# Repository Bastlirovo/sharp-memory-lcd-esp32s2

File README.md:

# sharp-memory-lcd-esp32s2
Project for ESP32-S2 devboard with connector for Sharp Memory LCD

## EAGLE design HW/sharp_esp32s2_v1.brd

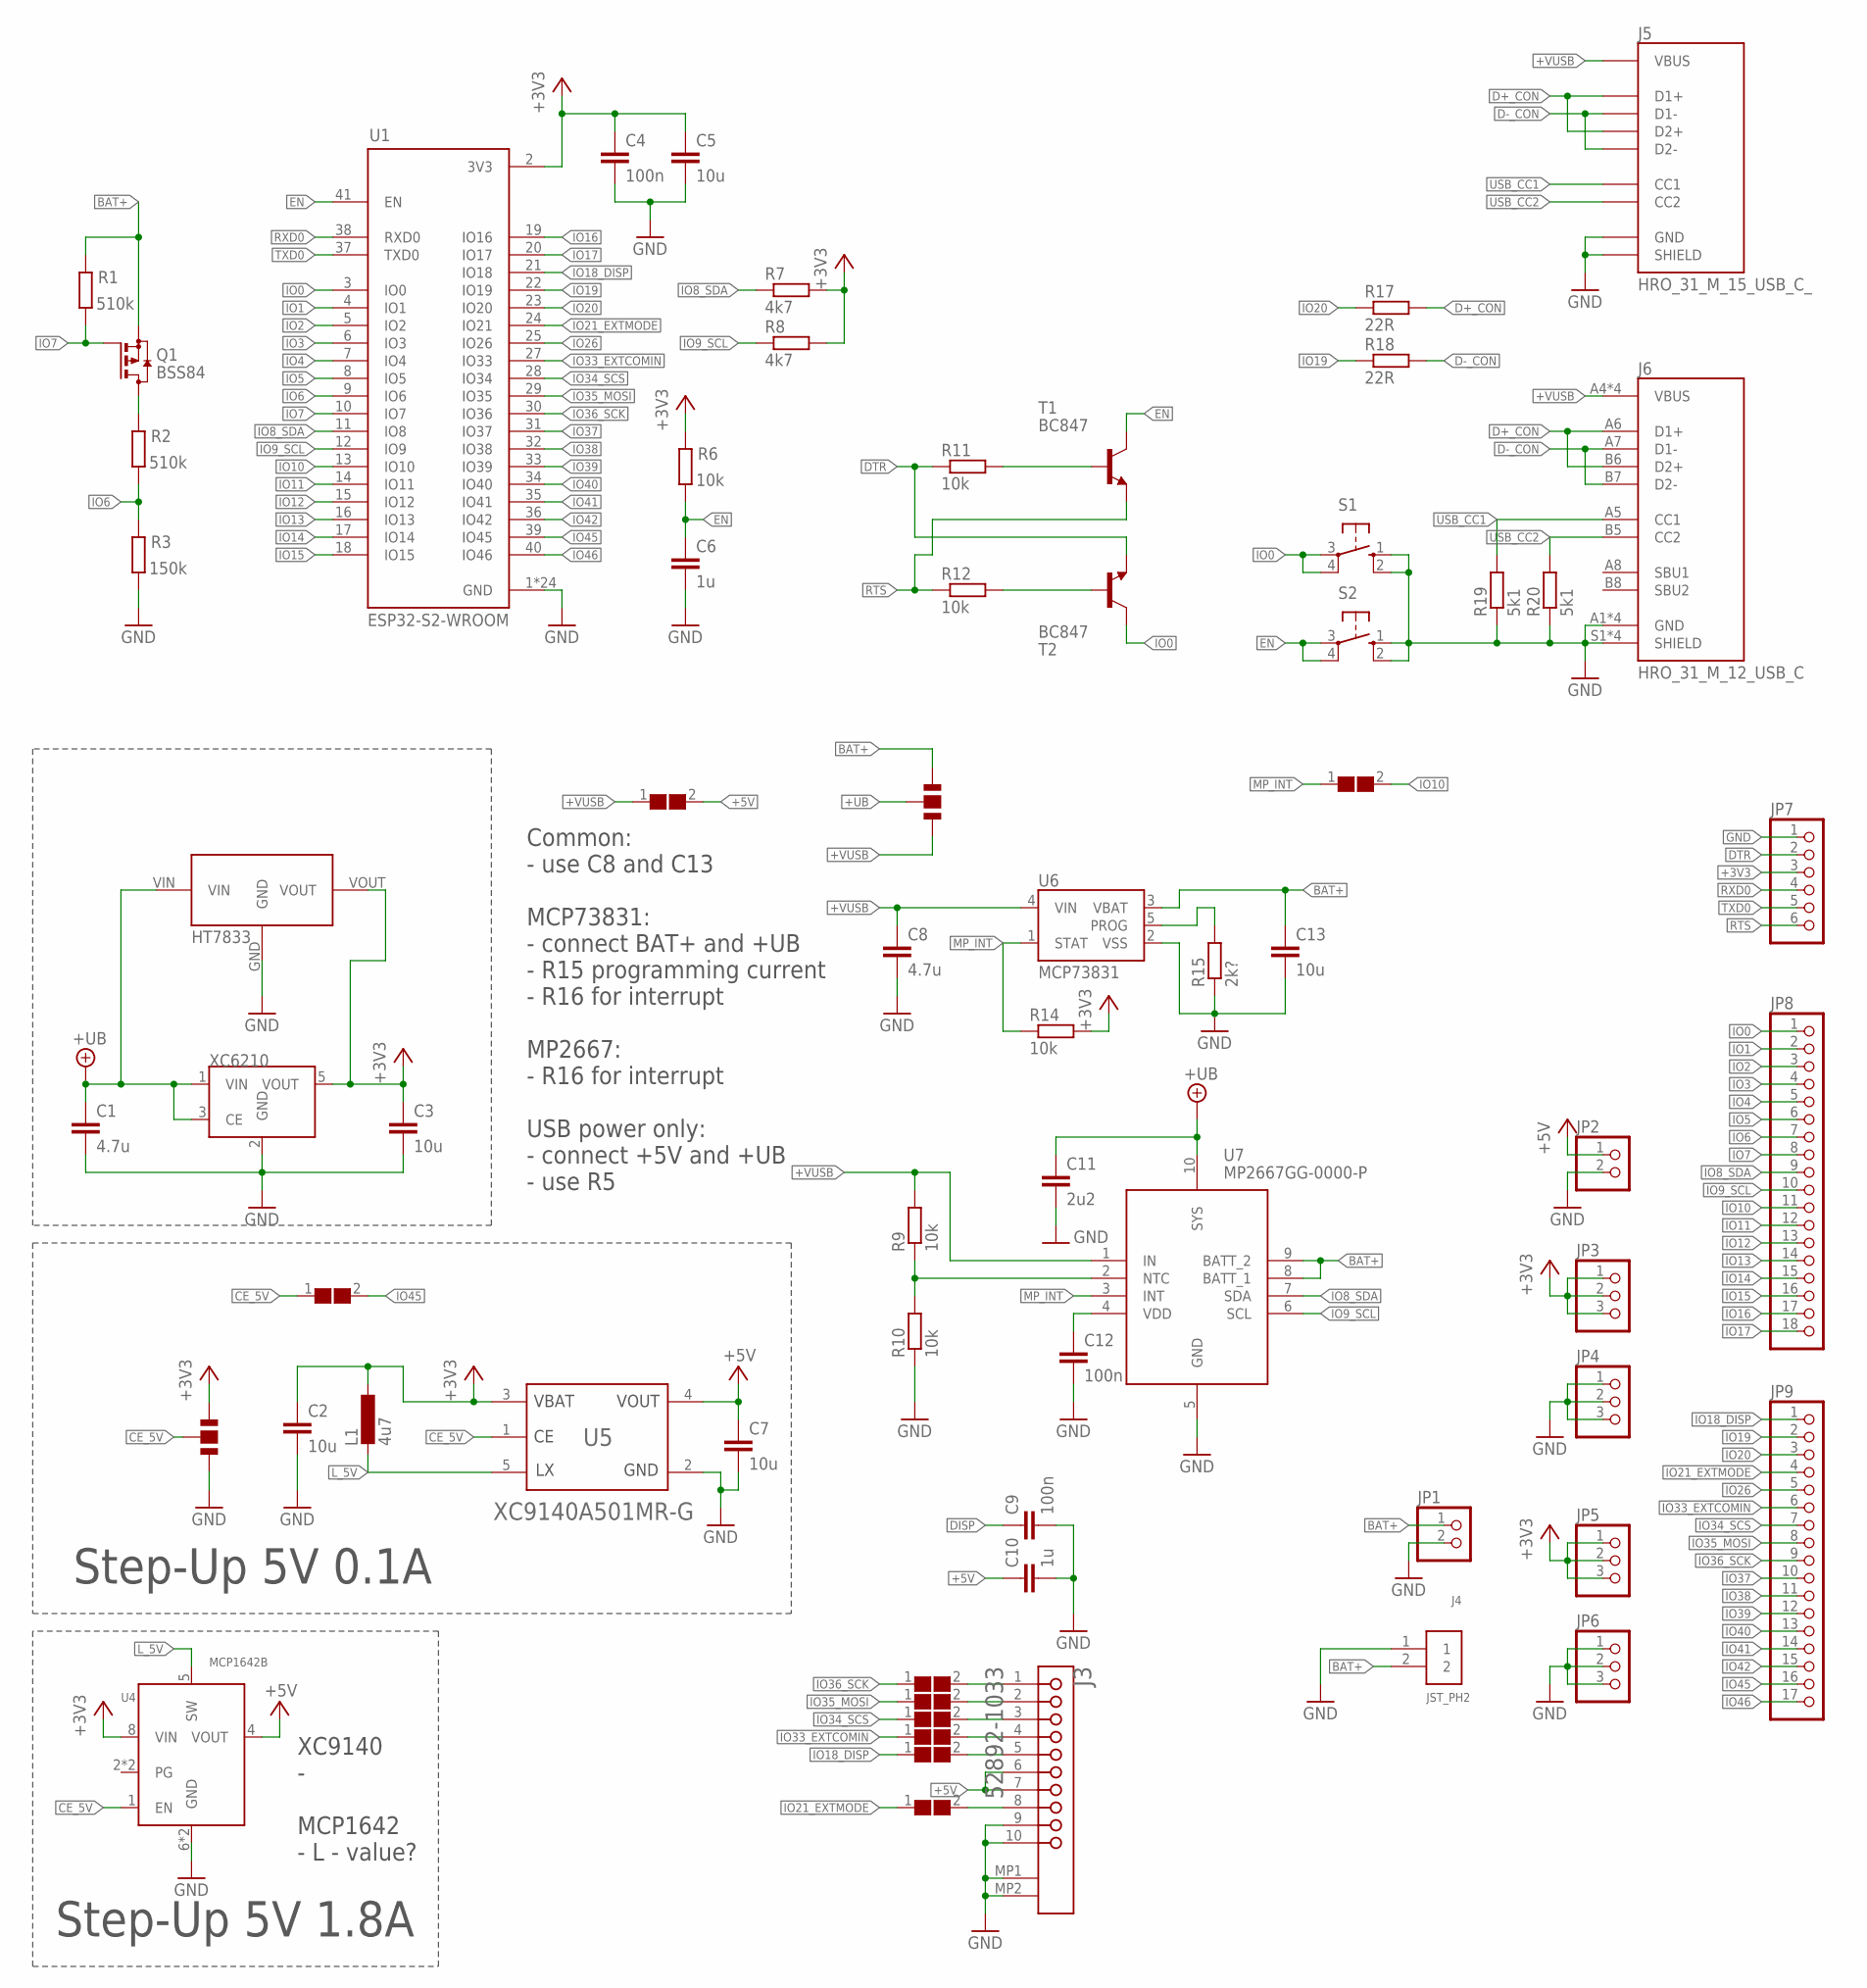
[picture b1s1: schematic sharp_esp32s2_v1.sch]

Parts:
C1, C8: 4.7u; C1206
C2, C7: 10u; C0603K
C3, C5, C13: 10u; C1206
C4, C9, C12: 100n; C0603K
C6, C10: 1u; C0603K
C11: 2u2; C1206
J1, J2: JUMPER; 2-WAY
J3: MOLEX_52892-1033MOLEX_52892-1033_0_0; MOLEX_52892-1033_0
J4: JST_PH2; JSTPH2
J5: HRO_31_M_15_USB_C_; HRO_31_M_15_USB_C
J6: HRO_31_M_12_USB_C
JP1, JP2: PINHD-1X2; 1X02
JP3, JP4, JP5, JP6: PINHD-1X3; 1X03
JP7: PINHD-1X6; 1X06
JP8: PINHD-1X18; 1X18
JP9: PINHD-1X17; 1X17
L1: 4u7; L3225M
Q1: BSS84; SOT23
R1, R2: 510k; R0603
R3: 150k; R0603
R6, R9, R10, R11, R12, R14: 10k; R0603
R7, R8: 4k7; R0603
R15: 2k?; R0603
R17, R18: 22R; R0603
R19, R20: 5k1; R0603
S1, S2: 10-XX; B3F-10XX
T1, T2: BC847; SOT23
U1: ESP32-S2-WROOM; XCVR_ESP32-S2-WROOM
U2: HT7833; SOT89
U3: XC6210; SOT-23-5
U4: MCP1642B; MSOP8
U5: TOREX_XC9140A501MR-GTOREX_XC9140A501MR-G_0_0; TOREX_XC9140A501MR-G_0
U6: MCP73831; SOT95P290X120-5
U7: MP2667GG-0000-P; QFN50P200X200X105-10N
U$1, U$2, U$3, U$4, U$5, U$6, U$7, U$8, U$9: SOLDER_JUMPER

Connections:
+3V3: C2.1, C3.1, C4.1, C5.1, J1.P$3, JP3.1, JP3.2, JP3.3, JP5.1, JP5.2, JP5.3, JP7.3, L1.1, R6.2, R7.2, R8.2, R14.2, U1.2 (3V3), U2.VOUT, U3.5 (VOUT), U4.8 (VIN), U5.3 (VBAT)
+5V: C7.1, C10.1, J3.6, J3.7, JP2.1, U4.4 (VOUT), U5.4 (VOUT), U$7.2
+UB: C1.1, C11.1, J2.P$1, U2.VIN, U3.1 (VIN), U3.3 (CE), U7.10 (SYS)
+VUSB: C8.1, J2.P$2, J5.P$2 (VBUS), J5.P$6 (VBUS), J5.P$9 (VBUS), J5.P$13 (VBUS), J6.A4 (VBUS), J6.A9 (VBUS), J6.B4 (VBUS), J6.B9 (VBUS), R9.2, U6.4 (VIN), U7.1 (IN), U$7.1
BAT+: C13.1, J2.P$3, J4.2, JP1.1, Q1.2 (S), R1.2, U6.3 (VBAT), U7.8 (BATT_1), U7.9 (BATT_2)
CE_5V: J1.P$1, U4.1 (EN), U5.1 (CE), U$9.1
D+_CON: J5.P$4 (D1+), J5.P$11 (D2+), J6.A6 (D1+), J6.B6 (D2+), R17.2
D-_CON: J5.P$3 (D1-), J5.P$10 (D2-), J6.A7 (D1-), J6.B7 (D2-), R18.2
DISP: C9.1, J3.5, U$5.2
DTR: JP7.2, R11.1, T2.2 (E)
EN: C6.1, R6.1, S2.3, S2.4 (P1), T1.3 (C), U1.41 (EN)
GND: C1.2, C2.2, C3.2, C4.2, C5.2, C6.2, C7.2, C8.2, C9.2, C10.2, C11.2, C12.2, C13.2, J1.P$2, J3.9, J3.10, J3.MP1, J3.MP2, J4.1, J5.P$1 (GND), J5.P$7 (GND), J5.P$8 (GND), J5.P$14 (GND), J5.P$15 (SHIELD), J5.P$16 (SHIELD), J5.P$17 (SHIELD), J5.P$18 (SHIELD), J6.A1 (GND), J6.A12 (GND), J6.B1 (GND), J6.B12 (GND), J6.S1 (SHIELD), J6.S2 (SHIELD), J6.S3 (SHIELD), J6.S4 (SHIELD), JP1.2, JP2.2, JP4.1, JP4.2, JP4.3, JP6.1, JP6.2, JP6.3, JP7.1, R3.1, R10.1, R15.1, R19.1, R20.1, S1.1 (S), S1.2 (S1), S2.1 (S), S2.2 (S1), U1.1 (GND), U1.26 (GND), U1.42 (GND), U1.43.1 (GND), U1.43.2 (GND), U1.43.3 (GND), U1.43.4 (GND), U1.43.5 (GND), U1.43.6 (GND), U1.43.7 (GND), U1.43.8 (GND), U1.43.9 (GND), U1.43.10 (GND), U1.43.11 (GND), U1.43.12 (GND), U1.43.13 (GND), U1.43.14 (GND), U1.43.15 (GND), U1.43.16 (GND), U1.43.17 (GND), U1.43.18 (GND), U1.43.19 (GND), U1.43.20 (GND), U1.43.21 (GND), U2.GND, U3.2 (GND), U4.6 (GND), U4.7 (GND), U5.2 (GND), U6.2 (VSS), U7.5 (GND)
IO0: JP8.1, S1.3, S1.4 (P1), T2.3 (C), U1.3 (IO0)
IO1: JP8.2, U1.4 (IO1)
IO2: JP8.3, U1.5 (IO2)
IO3: JP8.4, U1.6 (IO3)
IO4: JP8.5, U1.7 (IO4)
IO5: JP8.6, U1.8 (IO5)
IO6: JP8.7, R2.1, R3.2, U1.9 (IO6)
IO7: JP8.8, Q1.1 (G), R1.1, U1.10 (IO7)
IO8_SDA: JP8.9, R7.1, U1.11 (IO8), U7.7 (SDA)
IO9_SCL: JP8.10, R8.1, U1.12 (IO9), U7.6 (SCL)
IO10: JP8.11, U1.13 (IO10), U$8.2
IO11: JP8.12, U1.14 (IO11)
IO12: JP8.13, U1.15 (IO12)
IO13: JP8.14, U1.16 (IO13)
IO14: JP8.15, U1.17 (IO14)
IO15: JP8.16, U1.18 (IO15)
IO16: JP8.17, U1.19 (IO16)
IO17: JP8.18, U1.20 (IO17)
IO18_DISP: JP9.1, U1.21 (IO18), U$5.1
IO19: JP9.2, R18.1, U1.22 (IO19)
IO20: JP9.3, R17.1, U1.23 (IO20)
IO21_EXTMODE: JP9.4, U1.24 (IO21), U$6.1
IO26: JP9.5, U1.25 (IO26)
IO33_EXTCOMIN: JP9.6, U1.27 (IO33), U$4.1
IO34_SCS: JP9.7, U1.28 (IO34), U$3.1
IO35_MOSI: JP9.8, U1.29 (IO35), U$2.1
IO36_SCK: JP9.9, U1.30 (IO36), U$1.1
IO37: JP9.10, U1.31 (IO37)
IO38: JP9.11, U1.32 (IO38)
IO39: JP9.12, U1.33 (IO39)
IO40: JP9.13, U1.34 (IO40)
IO41: JP9.14, U1.35 (IO41)
IO42: JP9.15, U1.36 (IO42)
IO45: JP9.16, U1.39 (IO45), U$9.2
IO46: JP9.17, U1.40 (IO46)
L_5V: L1.2, U4.5 (SW), U5.5 (LX)
MP_INT: R14.1, U6.1 (STAT), U7.3 (INT), U$8.1
unnamed: J3.2, U$2.2
unnamed: J3.3, U$3.2
unnamed: J3.4, U$4.2
unnamed: Q1.3 (D), R2.2
unnamed: J3.8, U$6.2
unnamed: R9.1, R10.2, U7.2 (NTC)
unnamed: R15.2, U6.5 (PROG)
unnamed: C12.1, U7.4 (VDD)
unnamed: R12.2, T2.1 (B)
unnamed: R11.2, T1.1 (B)
RTS: JP7.6, R12.1, T1.2 (E)
RXD0: JP7.4, U1.38 (RXD0)
SCK: J3.1, U$1.2
TXD0: JP7.5, U1.37 (TXD0)
USB_CC1: J5.P$5 (CC1), J6.A5 (CC1), R19.2
USB_CC2: J5.P$12 (CC2), J6.B5 (CC2), R20.2

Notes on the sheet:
Step-Up 5V 1.8A
Step-Up 5V 0.1A
Common: - use C8 and C13 MCP73831: - connect BAT+ and +UB - R15 programming current - R16 for interrupt MP2667: - R16 for interrupt USB power only: - connect +5V and +UB - use R5
XC9140 - MCP1642 - L - value?

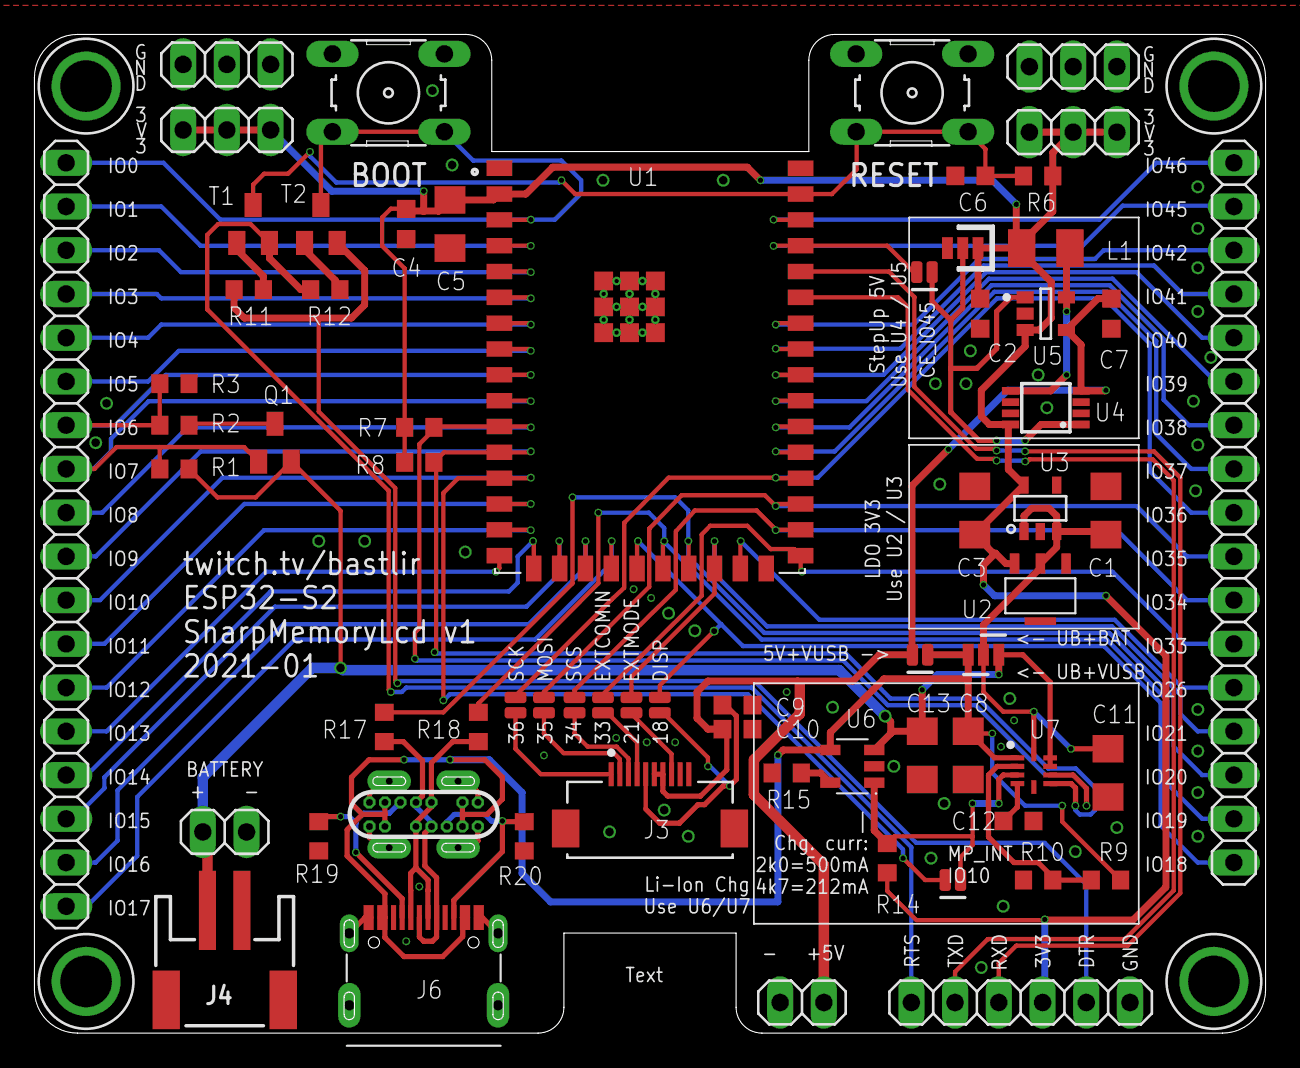
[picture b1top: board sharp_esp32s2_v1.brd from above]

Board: 2 copper layers, 71.5 x 58.0 mm, 66 parts (0 on the bottom side), 65 nets.

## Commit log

2021-02-14 Initial commit of v1 HW
2021-02-14 Added PDF with solder pads manual
2021-02-17 Added example with WiFi and I2C scanners on LCD.
2021-03-03 Commit of 3D models for Sharp ESP Box
2021-11-17 Added 3D model of box using 18650 battery
    Photos on https://www.instagram.com/p/CPtF8xuLmJq/
